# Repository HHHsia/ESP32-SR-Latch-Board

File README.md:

# ESP32-SR-Latch-Board  
集ESP32 MCU、Shift Register、Latch 矩陣、LED於一體，共16單元

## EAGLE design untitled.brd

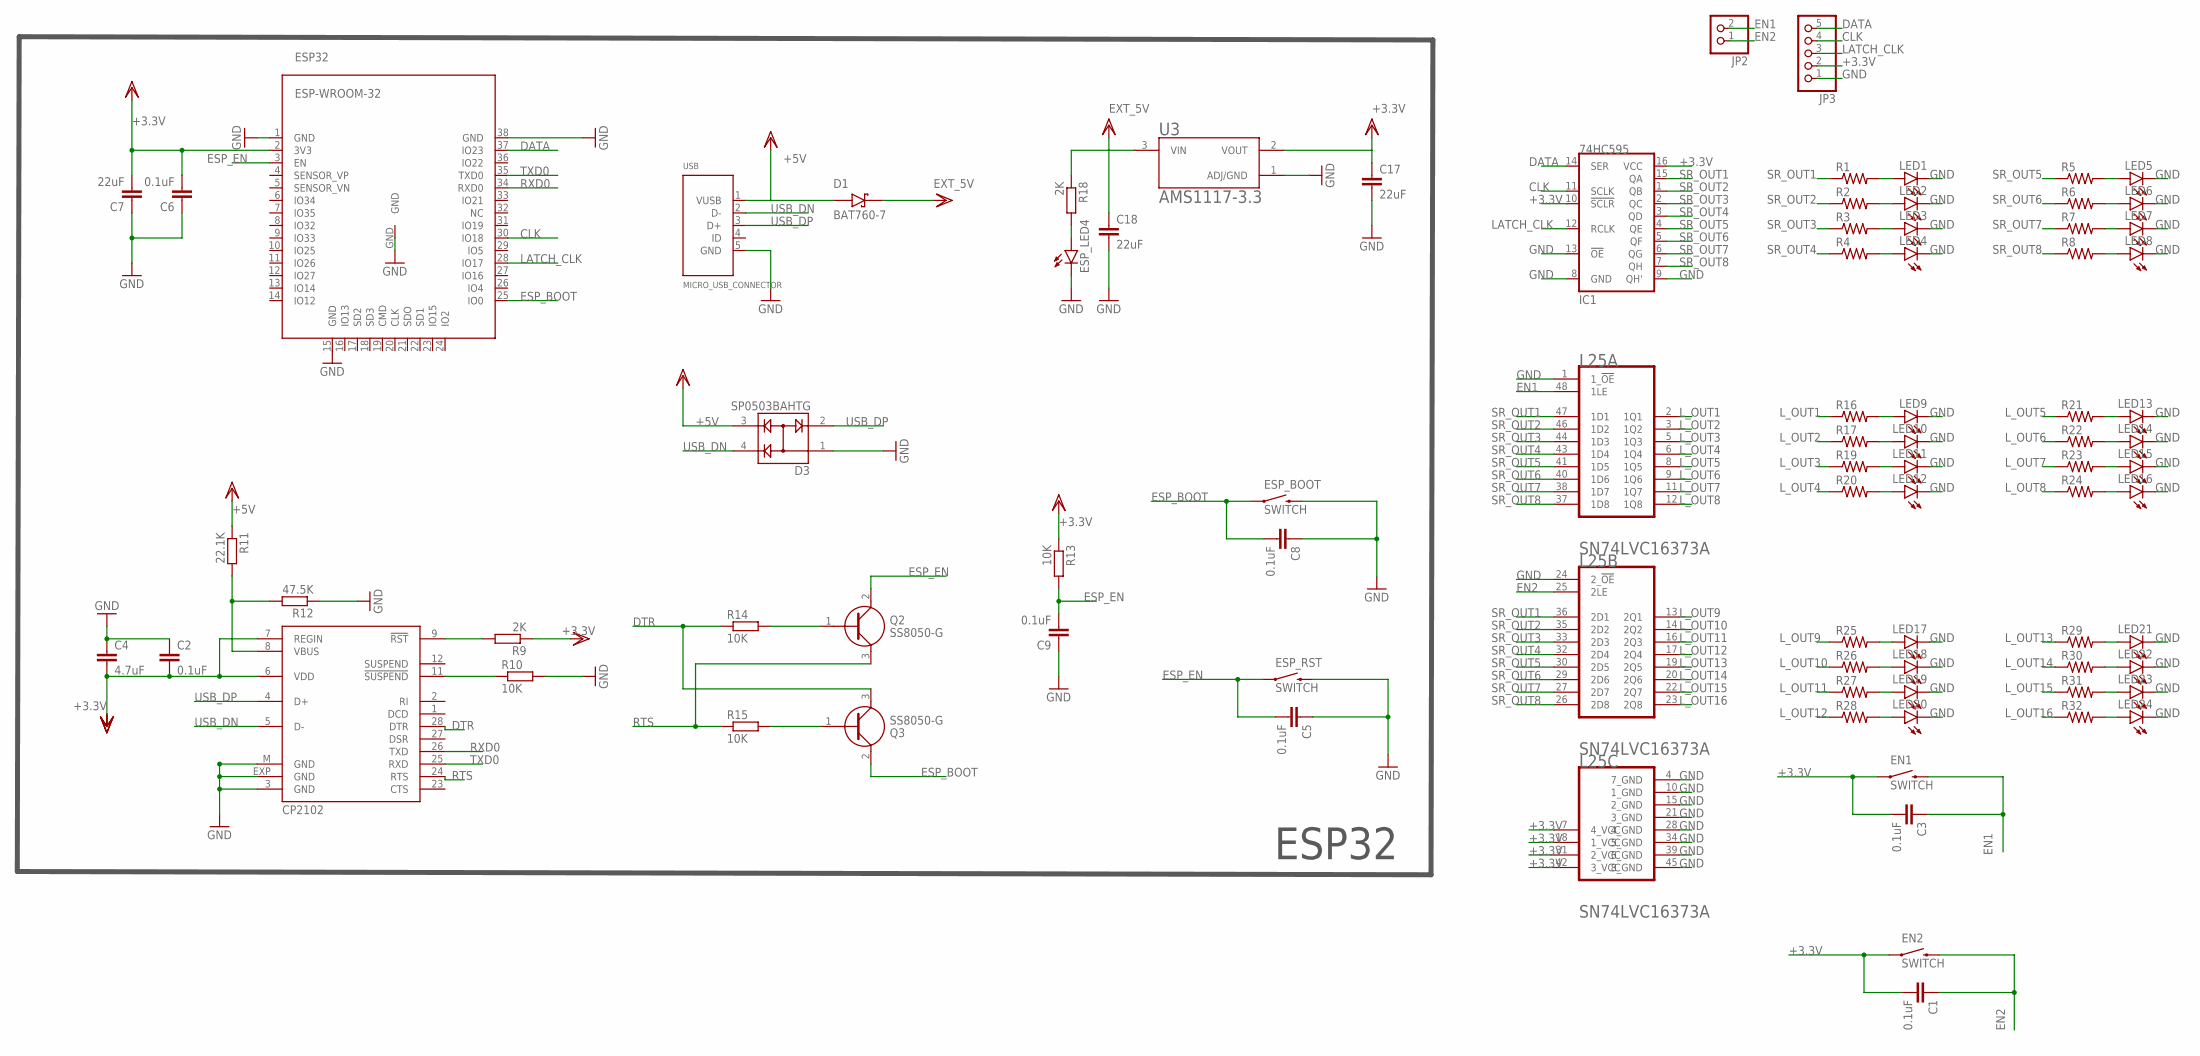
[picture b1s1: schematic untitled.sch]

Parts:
C1, C2, C3, C5, C6, C8, C9: 0.1uF; C0805
C4: 4.7uF; C0805
C7, C17, C18: 22uF; C0805
D1: BAT760-7; SOD2513X120N
D3: SP0503BAHTG; SOT143
EN1, EN2: SWITCH; SWITCH_2PIN
ESP32: ESP-WROOM-32
ESP_BOOT: SWITCH; SWITCH_2PIN
ESP_LED4: LEDCHIPLED_0805; CHIPLED_0805
ESP_RST: SWITCH; SWITCH_2PIN
IC1: 74HC595; SO16
IC3: CP2102; MLP28
JP2: PINHD-1X2; 1X02
JP3: PINHD-1X5; 1X05
L25: TEXAS_INSTRUMENTS_SN74LVC16373ATEXAS_INSTRUMENTS_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; TEXAS_INSTRUMENTS_SN74LVC16373A_2
LED1, LED2, LED3, LED4, LED5, LED6, LED7, LED8, LED9, LED10, LED11, LED12, LED13, LED14, LED15, LED16, LED17, LED18, LED19, LED20, LED21, LED22, LED23, LED24: LEDCHIPLED_0805; CHIPLED_0805
Q2, Q3: SS8050-G; MBTB-T-SOT23
R1, R2, R3, R4, R5, R6, R7, R8, R16, R17, R19, R20, R21, R22, R23, R24, R25, R26, R27, R28, R29, R30, R31, R32: R-US_R0805; R0805
R9, R18: 2K; R0805
R10, R13, R14, R15: 10K; R0805
R11: 22.1K; R0805
R12: 47.5K; R0805
U3: AMS1117-3.3; SOT229P700X180-4N
USB: MICRO_USB_CONNECTOR; MICRO_USB_4LEGS

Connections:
+3.3V: C1.2, C2.2, C3.2, C4.2, C6.2, C7.2, C17.1, EN1.1, EN2.1, ESP32.2 (3V3), IC1.10 (!SCLR), IC1.16 (VCC), IC3.6 (VDD), IC3.7 (REGIN), JP3.2, L25.7 (4_VCC), L25.18 (1_VCC), L25.31 (2_VCC), L25.42 (3_VCC), R9.1, R13.1, U3.2 (VOUT)
+5V: D1.A, D3.3, R11.1, USB.1 (VUSB)
CLK: ESP32.30 (IO18), IC1.11 (SCLK), JP3.4
DATA: ESP32.37 (IO23), IC1.14 (SER), JP3.5
DTR: IC3.28 (DTR), Q3.3 (C), R14.1
EN1: C3.1, EN1.2, JP2.2, L25.48 (1LE)
EN2: C1.1, EN2.2, JP2.1, L25.25 (2LE)
ESP_BOOT: C8.2, ESP32.25 (IO0), ESP_BOOT.1, Q3.2 (E)
ESP_EN: C5.2, C9.2, ESP32.3 (EN), ESP_RST.1, Q2.2 (E), R13.2
EXT_5V: C18.1, D1.C (K), R18.1, U3.3 (VIN)
GND: C2.1, C4.1, C5.1, C6.1, C7.1, C8.1, C9.1, C17.2, C18.2, D3.1, ESP32.1 (GND), ESP32.15 (GND), ESP32.38 (GND), ESP32.GND, ESP_BOOT.2, ESP_LED4.C, ESP_RST.2, IC1.8 (GND), IC1.9 (QH'), IC1.13 (!OE), IC3.3 (GND), IC3.EXP (GND), IC3.M (GND), JP3.1, L25.1 (1_!OE!), L25.4 (7_GND), L25.10 (1_GND), L25.15 (2_GND), L25.21 (3_GND), L25.24 (2_!OE!), L25.28 (4_GND), L25.34 (5_GND), L25.39 (6_GND), L25.45 (8_GND), LED1.C, LED2.C, LED3.C, LED4.C, LED5.C, LED6.C, LED7.C, LED8.C, LED9.C, LED10.C, LED11.C, LED12.C, LED13.C, LED14.C, LED15.C, LED16.C, LED17.C, LED18.C, LED19.C, LED20.C, LED21.C, LED22.C, LED23.C, LED24.C, R10.2, R12.1, U3.1 (ADJ/GND), USB.5 (GND)
LATCH_CLK: ESP32.28 (IO17), IC1.12 (RCLK), JP3.3
L_OUT1: L25.2 (1Q1), R16.1
L_OUT2: L25.3 (1Q2), R17.1
L_OUT3: L25.5 (1Q3), R19.1
L_OUT4: L25.6 (1Q4), R20.1
L_OUT5: L25.8 (1Q5), R21.1
L_OUT6: L25.9 (1Q6), R22.1
L_OUT7: L25.11 (1Q7), R23.1
L_OUT8: L25.12 (1Q8), R24.1
L_OUT9: L25.13 (2Q1), R25.1
L_OUT10: L25.14 (2Q2), R26.1
L_OUT11: L25.16 (2Q3), R27.1
L_OUT12: L25.17 (2Q4), R28.1
L_OUT13: L25.19 (2Q5), R29.1
L_OUT14: L25.20 (2Q6), R30.1
L_OUT15: L25.22 (2Q7), R31.1
L_OUT16: L25.23 (2Q8), R32.1
unnamed: LED1.A, R1.2
unnamed: LED2.A, R2.2
unnamed: LED3.A, R3.2
unnamed: LED4.A, R4.2
unnamed: LED5.A, R5.2
unnamed: LED6.A, R6.2
unnamed: IC3.11 (!SUSPEND), R10.1
unnamed: IC3.8 (VBUS), R11.2, R12.2
unnamed: Q2.1 (B), R14.2
unnamed: Q3.1 (B), R15.2
unnamed: LED7.A, R7.2
unnamed: LED8.A, R8.2
unnamed: ESP_LED4.A, R18.2
unnamed: LED9.A, R16.2
unnamed: LED10.A, R17.2
unnamed: LED11.A, R19.2
unnamed: LED12.A, R20.2
unnamed: LED13.A, R21.2
unnamed: IC3.9 (!RST), R9.2
unnamed: LED14.A, R22.2
unnamed: LED15.A, R23.2
unnamed: LED16.A, R24.2
unnamed: LED17.A, R25.2
unnamed: LED18.A, R26.2
unnamed: LED19.A, R27.2
unnamed: LED20.A, R28.2
unnamed: LED21.A, R29.2
unnamed: LED22.A, R30.2
unnamed: LED23.A, R31.2
unnamed: LED24.A, R32.2
RTS: IC3.24 (RTS), Q2.3 (C), R15.1
RXD0: ESP32.34 (RXD0), IC3.26 (TXD)
SR_OUT1: IC1.15 (QA), L25.36 (2D1), L25.47 (1D1), R1.1
SR_OUT2: IC1.1 (QB), L25.35 (2D2), L25.46 (1D2), R2.1
SR_OUT3: IC1.2 (QC), L25.33 (2D3), L25.44 (1D3), R3.1
SR_OUT4: IC1.3 (QD), L25.32 (2D4), L25.43 (1D4), R4.1
SR_OUT5: IC1.4 (QE), L25.30 (2D5), L25.41 (1D5), R5.1
SR_OUT6: IC1.5 (QF), L25.29 (2D6), L25.40 (1D6), R6.1
SR_OUT7: IC1.6 (QG), L25.27 (2D7), L25.38 (1D7), R7.1
SR_OUT8: IC1.7 (QH), L25.26 (2D8), L25.37 (1D8), R8.1
TXD0: ESP32.35 (TXD0), IC3.25 (RXD)
USB_DN: D3.4, IC3.5 (D-), USB.2 (D-)
USB_DP: D3.2, IC3.4 (D+), USB.3 (D+)

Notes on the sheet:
ESP32

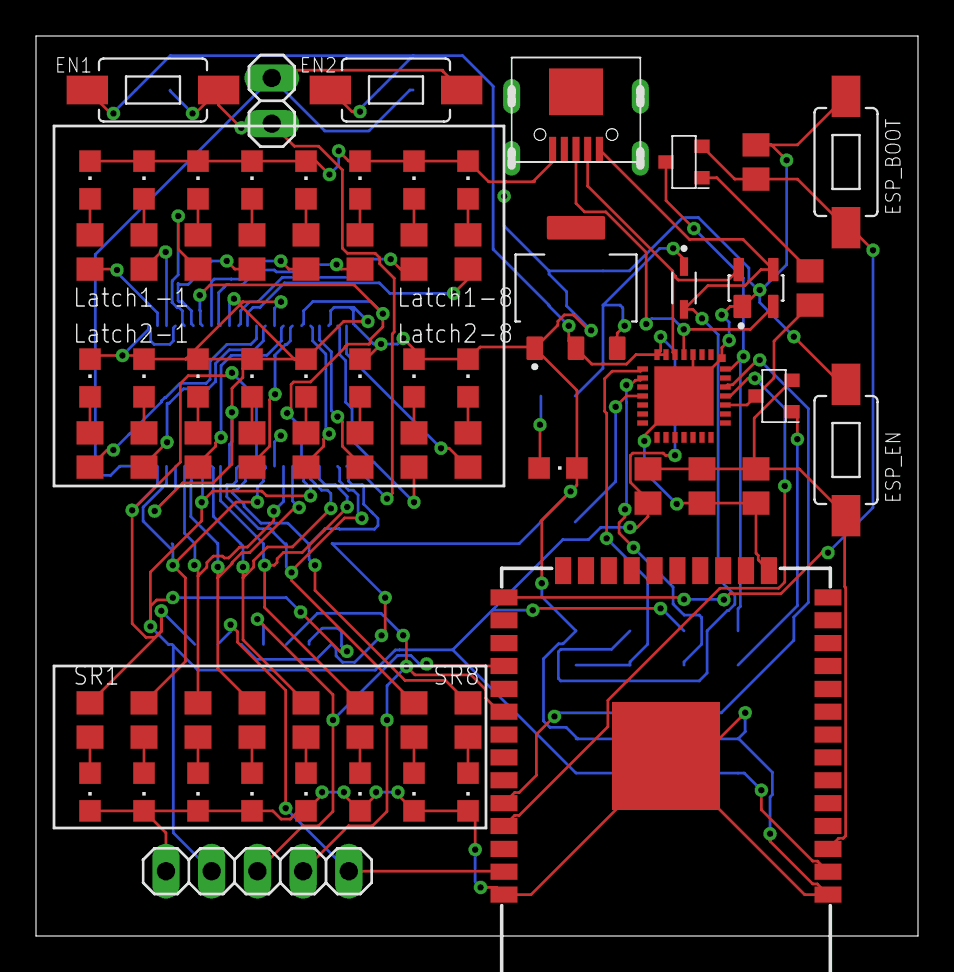
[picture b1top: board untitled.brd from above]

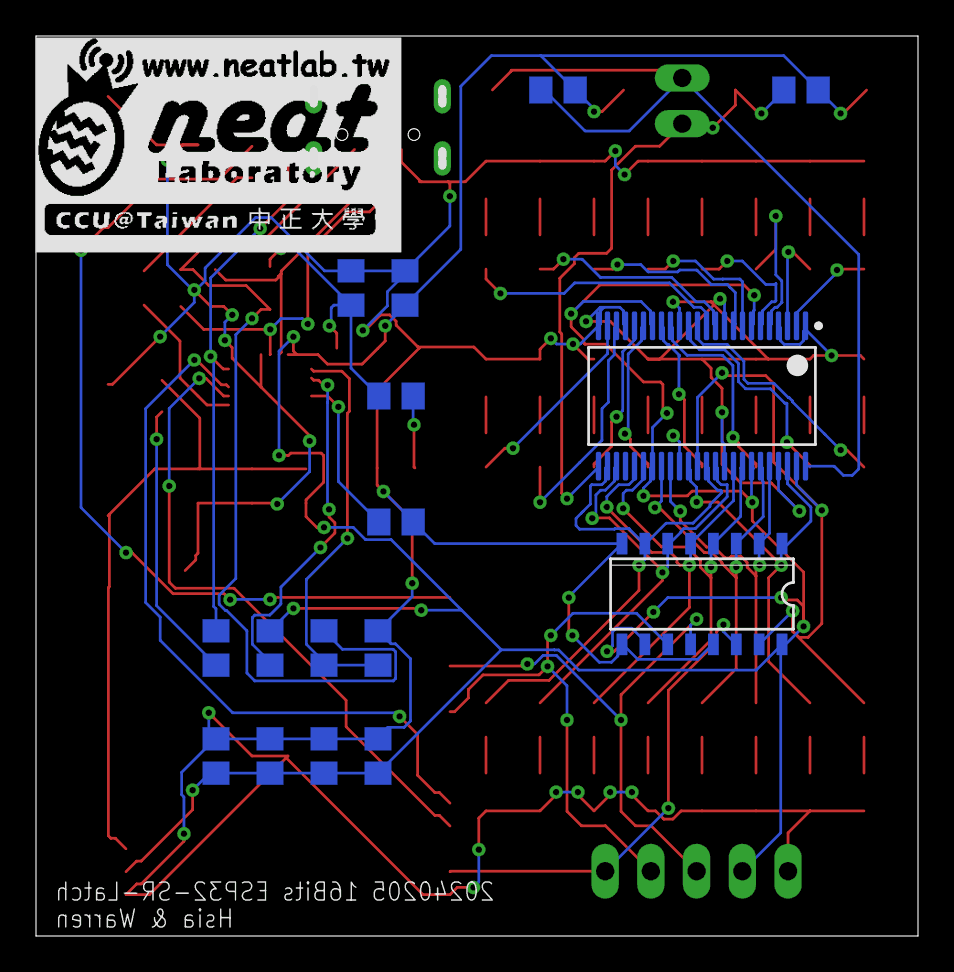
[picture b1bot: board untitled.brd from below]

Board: 2 copper layers, 48.5 x 49.5 mm, 85 parts (17 on the bottom side), 71 nets.

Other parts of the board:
U$1: LOGO_SCALE_2.0

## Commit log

2024-07-05 0705

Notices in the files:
parts and their libraries:
SparkFun-Aesthetics: Licensing: Creative Commons ShareAlike 4.0 International - https://creativecommons.org/licenses/by-sa/4.0
